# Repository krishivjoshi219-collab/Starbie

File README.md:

# Starbie — Straw Hat Edition

A custom pirate-themed interactive virtual pet console and environmental monitor powered by the Seeed Studio XIAO ESP32-C3 (based on the starbie)
so basically I don't how to write a readme.dm so it might be um worst :C 
---
## Images

---

## Hardware Features
Here we hard following components:
Mircrocontroller: I used a ESP32-C3 (I am new do i don't know much about mircrocontroller!!!!!)

Display: I used a 4 pin 0.96 OLED for displaying my luffy (i know that luffy is not a pet but uh whatever)

Push BUttons: I wired 2 push button on the side of the PCB so you can open the menu etc

Motion sensors: So luffy can react to any motion like falling etc

Temperature: Just shows the tempeature in the menu 

---

## Hardware Pinout

| Function / Component | XIAO Pin Label | ESP32-C3 GPIO | Notes |
| :--- | :--- | :--- | :--- |
| **DHT11 Data** | D0 | GPIO 2 | 10kΩ pull-up to +3.3V |
| **Button 1 (Menu)** | D2 | GPIO 4 | Active-Low (Internal Pull-Up) |
| **Button 2 (Stats)** | D3 | GPIO 5 | Active-Low (Internal Pull-Up) |
| **I2C SDA** | D4 | GPIO 6 | Shared by OLED and MPU-6050 |
| **I2C SCL** | D5 | GPIO 7 | Shared by OLED and MPU-6050 |
| **Buzzer Driver** | D6 | GPIO 21 | Switches NPN base via 1kΩ resistor |

---

## BOM

| Part | Description | Qty | Unit | Total | Vendor |
| :--- | :--- | :---: | :---: | :---: | :--- |
| **Seeed Studio XIAO ESP32-C3** | Main ESP32-C3 RISC-V microcontroller board with Wi-Fi and BLE | 1 | $9.33 | $9.33 | Robu.in |
| **0.96 inch Yellow-Blue OLED Display Module** | 0.96 inch I2C OLED screen for pet animation and stats HUD | 1 | $1.90 | $1.90 | Robu.in |
| **DHT11 Temperature & Humidity Sensor Module** | Digital temperature and humidity sensor module; wire to U2.1/U2.2/U2.4 | 1 | $0.63 | $0.63 | Robu.in |
| **SmartElex MPU-6050 6-Axis IMU Module** | 6-axis motion tracking sensor; wire to J3.1–J3.4 | 1 | $4.71 | $4.71 | Robu.in |
| **YMD12095 3V Active Buzzer (12x9.5mm)** | 3V active electromagnetic buzzer for BZ1 (not 5V) | 1 | $0.27 | $0.27 | Robu.in |
| **Tactile Push Button Switch 6x6x5 (Pack of 10)** | Momentary tactile push buttons; 2 used, 8 spares | 1 | $0.15 | $0.15 | Robu.in |
| **CFR25 10k Ohm Axial Resistors** | DHT11 data pull-up resistor (R1); 1 used, 6 spares | 7 | $0.017 | $0.12 | Robu.in |
| **MF25 1k Ohm Axial Resistors** | Buzzer NPN base resistor (R2); 1 used, 2 spares | 3 | $0.043 | $0.13 | Robu.in |
| **BC547 NPN Transistor TO-92** | NPN transistor switch for BZ1 (Q1); C-B-E pinout | 3 | $0.046 | $0.14 | Robu.in |
| **1N4148 Switching Diode DO-35** | Flyback protection diode for BZ1 (D1) | 7 | $0.036 | $0.25 | Robu.in |
| **1x40 Pin 2.54mm Male Berg Strip Connector** | Male pin headers for XIAO and module connections | 2 | $0.085 | $0.17 | Robu.in |
| **1x2 Pin 2.54mm Female Header** | J2 battery header; unused in USB-only build | 1 | $0.12 | $0.12 | Robu.in |
| **1x4 Pin 2.54mm Female Header** | J1 OLED socket | 1 | $0.13 | $0.13 | Robu.in |
| **1x8 Pin 2.54mm Female Header** | J3 MPU socket | 1 | $0.18 | $0.18 | Robu.in |
| **Male to Female Jumper Wires 40pcs 20cm** | Jumper wires for DHT11 and MPU | 1 | $0.52 | $0.52 | Robu.in |
| **Robu PCB Manufacturing Service (5 pcs)** | 5 custom 2-layer Starbie boards; 84.77 × 84.65 mm; 1.6 mm; HASL; green | 1 | $9.55 | $9.55 | Robu.in |
| **Tax & shipping** | PCB shipping ₹49; components shipping free; tax ₹0 | - | - | $0.52 | Robu.in |
| **Total** | | | | **$28.79** | **Total $28.79 of $30 tier 1 funding (₹2,713.97 at ₹94.26/$)** |

Exact conversion: ₹2,713.97 ÷ 94.26 = $28.7924. Line prices are rounded to cents. Orders: Robu #3812423 (components) and #3812451 (PCB). USB-C data cable already owned; not included.

---

## Firmware Setup

1. Install the Arduino IDE grant it permission to run it
2. open `firmware/Starbie/Starbie.ino` in the Arduino IDE.
3. Install the board in the IDE (esp32 by espreesif system)
 Select **XIAO_ESP32C3** under **Tools → Board → esp32**.
4. IInstall the following via Library Manager:
   * `Adafruit GFX Library`
   * `Adafruit SSD1306`
   * `Adafruit MPU6050`
   * `DHT sensor library`
5. code is already compiling (i just used the starbie frimware from the guide !!!)
6. Make sure that your microcontroller is connected to a USB 3 and push the code and BOOM!! your starbie is ready (provided that you already made the circut on a PCB!!)

---
## How I made It !
First of all i am a beginner who is doing his first hardware project and first project without the use of AI (exluding writng C++ in the arduino IDE it is well under the 30% ai limit)

This is the first time i am writing a README.md !! 

I was seriously like oh i could even do all this !! when i first opened the kicad for half life

Half Life is my first ysws and first project in which use of ai was minimal but still it was hard for me !!

But it was really fun too !!
I started this week late just on wed and that also cuz of schools etc i was busy right now too!!

KiCAD is now really easy for me it doesn't feel like a new world now !!:D 

But i had many dificuties too very much so this time instead of vibe coding i did everything myself just took help of the ai by asking questions like "How to do this ?" etc but i did the entire designing part myself and also i was really scarded like just how to write a README !!!!!!!!

But now it feels easy !!

And also i am able to explain the entire project myself !

---
# Most Boring parts

What i found most boring was adding silkscreen !!
Other than it i enjoyed everything most of ig

And solving the errors in the PCB design was the most frustating part !!! that 64nm error i talked about in my journal !!

---
# Most Fun part
Most fun part as PCB routing and adding the edge.cuts as the straw hats !!!!!!!!!!

After that i enjoyed the schemetic too and i generally enjoyed the debugging the KiCad errors too !

---
## At last I want to thanks the hc ysws half life organizers for organizing such a great ysws and giving me the opportinity to learn !!

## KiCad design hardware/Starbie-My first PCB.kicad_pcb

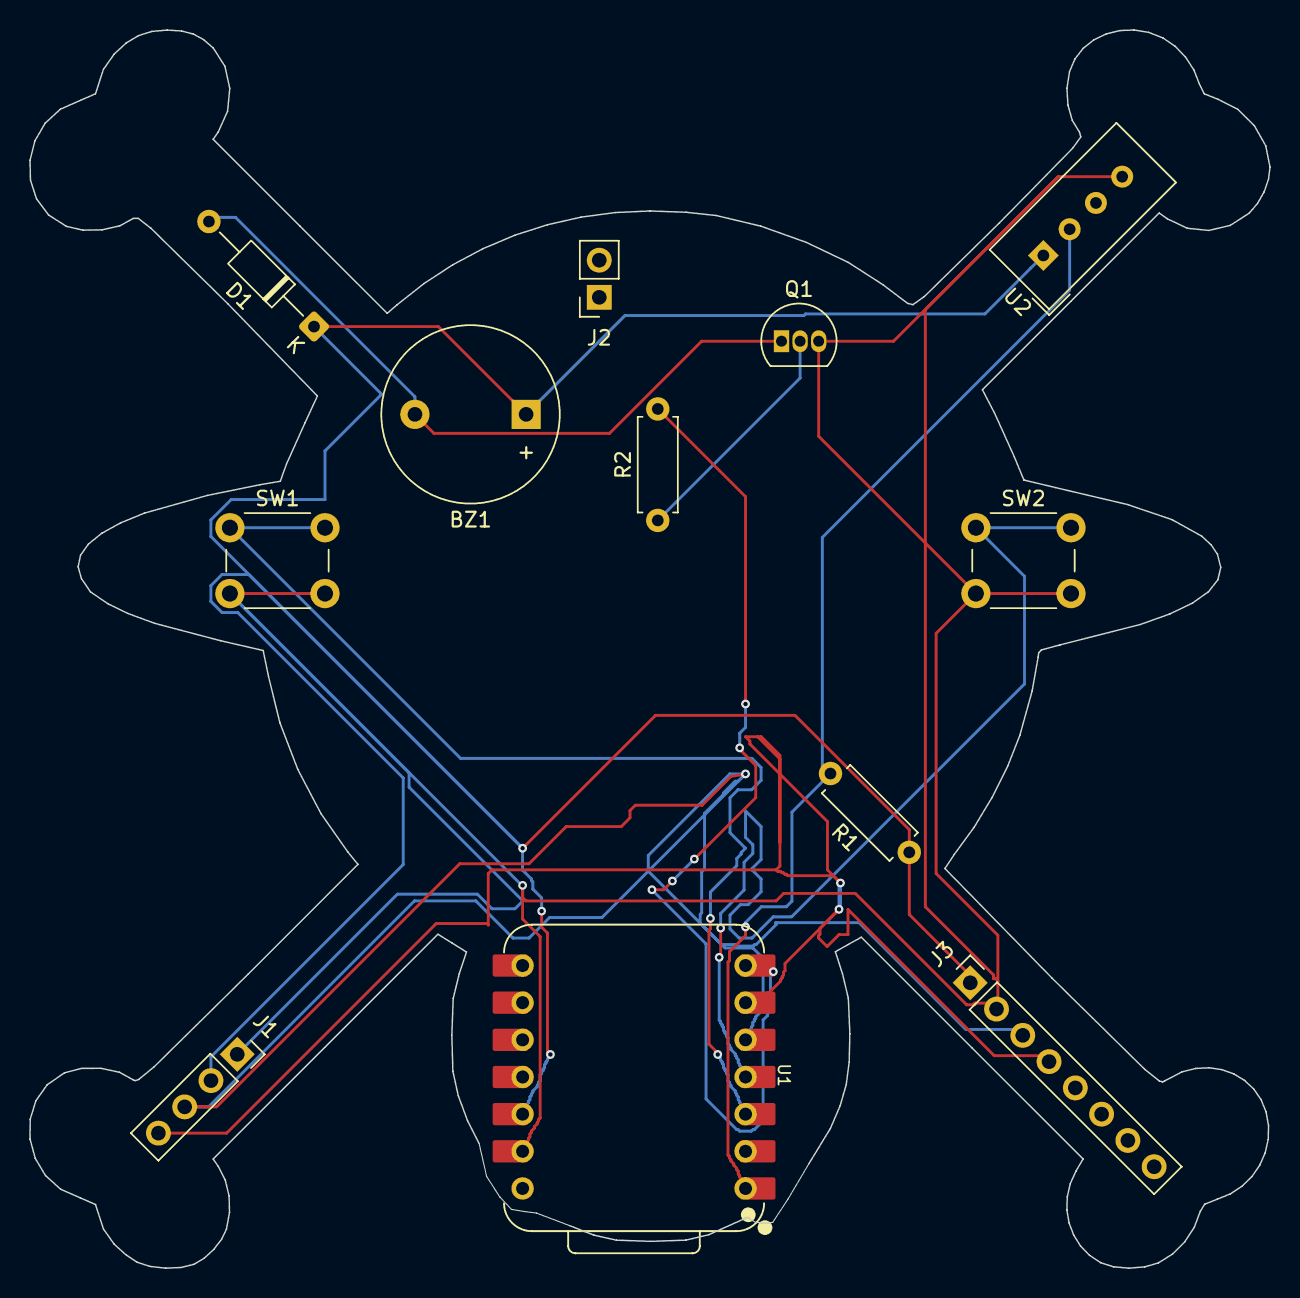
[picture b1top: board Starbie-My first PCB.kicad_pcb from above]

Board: 2 copper layers, 84.8 x 84.6 mm, 12 parts (0 on the bottom side), 10 nets.

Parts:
BZ1: Buzzer; Buzzer_12x9.5RM7.6
D1: D; D_DO-35_SOD27_P10.16mm_Horizontal
J1: Conn_01x04_Pin; PinSocket_1x04_P2.54mm_Vertical
J2: Conn_01x02_Pin; PinSocket_1x02_P2.54mm_Vertical
J3: Conn_01x08_Pin; PinSocket_1x08_P2.54mm_Vertical
Q1: Q_NPN_CBE; TO-92L_Inline
R1: 10k; R_Axial_DIN0207_L6.3mm_D2.5mm_P7.62mm_Horizontal
R2: R; R_Axial_DIN0207_L6.3mm_D2.5mm_P7.62mm_Horizontal
SW1, SW2: SW_Push; SW_PUSH_6mm
U1: XIAO-ESP32-C3-SMD; XIAO-ESP32-C6-DIP
U2: DHT11; Aosong_DHT11_5.5x12.0_P2.54mm

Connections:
+3.3V: BZ1.1 (+), D1.1 (K), J1.2, J3.1, R1.1, U1.12 (3V3_OUT), U2.1 (VDD)
/DHT11 Data: R1.2, U1.1 (D0), U2.2 (DATA)
/GPI02: SW1.1, U1.3 (D2)
/GPI03: SW2.1, U1.4 (D3)
/R1: Q1.2 (B), R2.1
/R2: R2.2, U1.7 (D6)
/SCL: J1.3, J3.3, U1.5 (D4)
/SDA: J1.4, J3.4, U1.6 (D5)
GND: J1.1, J3.2, Q1.3 (E), SW1.2, SW2.2, U1.13 (GND), U2.4 (GND)
unnamed: BZ1.2 (-), D1.2 (A), Q1.1 (C)
